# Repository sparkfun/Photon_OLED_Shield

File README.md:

SparkFun Photon OLED Shield
========================================

[*SparkFun Photon OLED Shield (DEV-13628)*](https://www.sparkfun.com/products/13628)

The [SparkFun Photon OLED Shield](https://www.sparkfun.com/products/13231) breaks out a small monochrome, blue-on-black OLED to use with your Photon module. Its micro, but it still packs a punch  the OLED display is crisp, and you can fit a deceivingly large amount of graphics on there. This shield is perfect for adding graphics to your Photon, displaying diagnostic information without resorting to serial output, and teaching a little game theory.

Repository Contents
-------------------

* **/Hardware** - Eagle design files (.brd, .sch)
* **/Production** - Production panel files (.brd)
* **/Libraries** - Firmware library and example code for the Particle Photon.

Documentation
--------------
* **[Hookup Guide](https://learn.sparkfun.com/tutorials/photon-oled-shield-hookup-guide)** - Hardware overview and example code.

Product Versions
----------------
* [DEV-13628](https://www.sparkfun.com/products/13628)- V1.0 release of the Photon OLED Shield.

License Information
-------------------
This product is _**open source**_! 

The **hardware** is released under [Creative Commons ShareAlike 4.0 International](https://creativecommons.org/licenses/by-sa/4.0/).

The **code**  license can be found in the source directory.

Please use, reuse, and modify these files as you see fit. Please maintain attribution to SparkFun Electronics and release anything derivative under the same license.

Distributed as-is; no warranty is given.

- Your friends at SparkFun.

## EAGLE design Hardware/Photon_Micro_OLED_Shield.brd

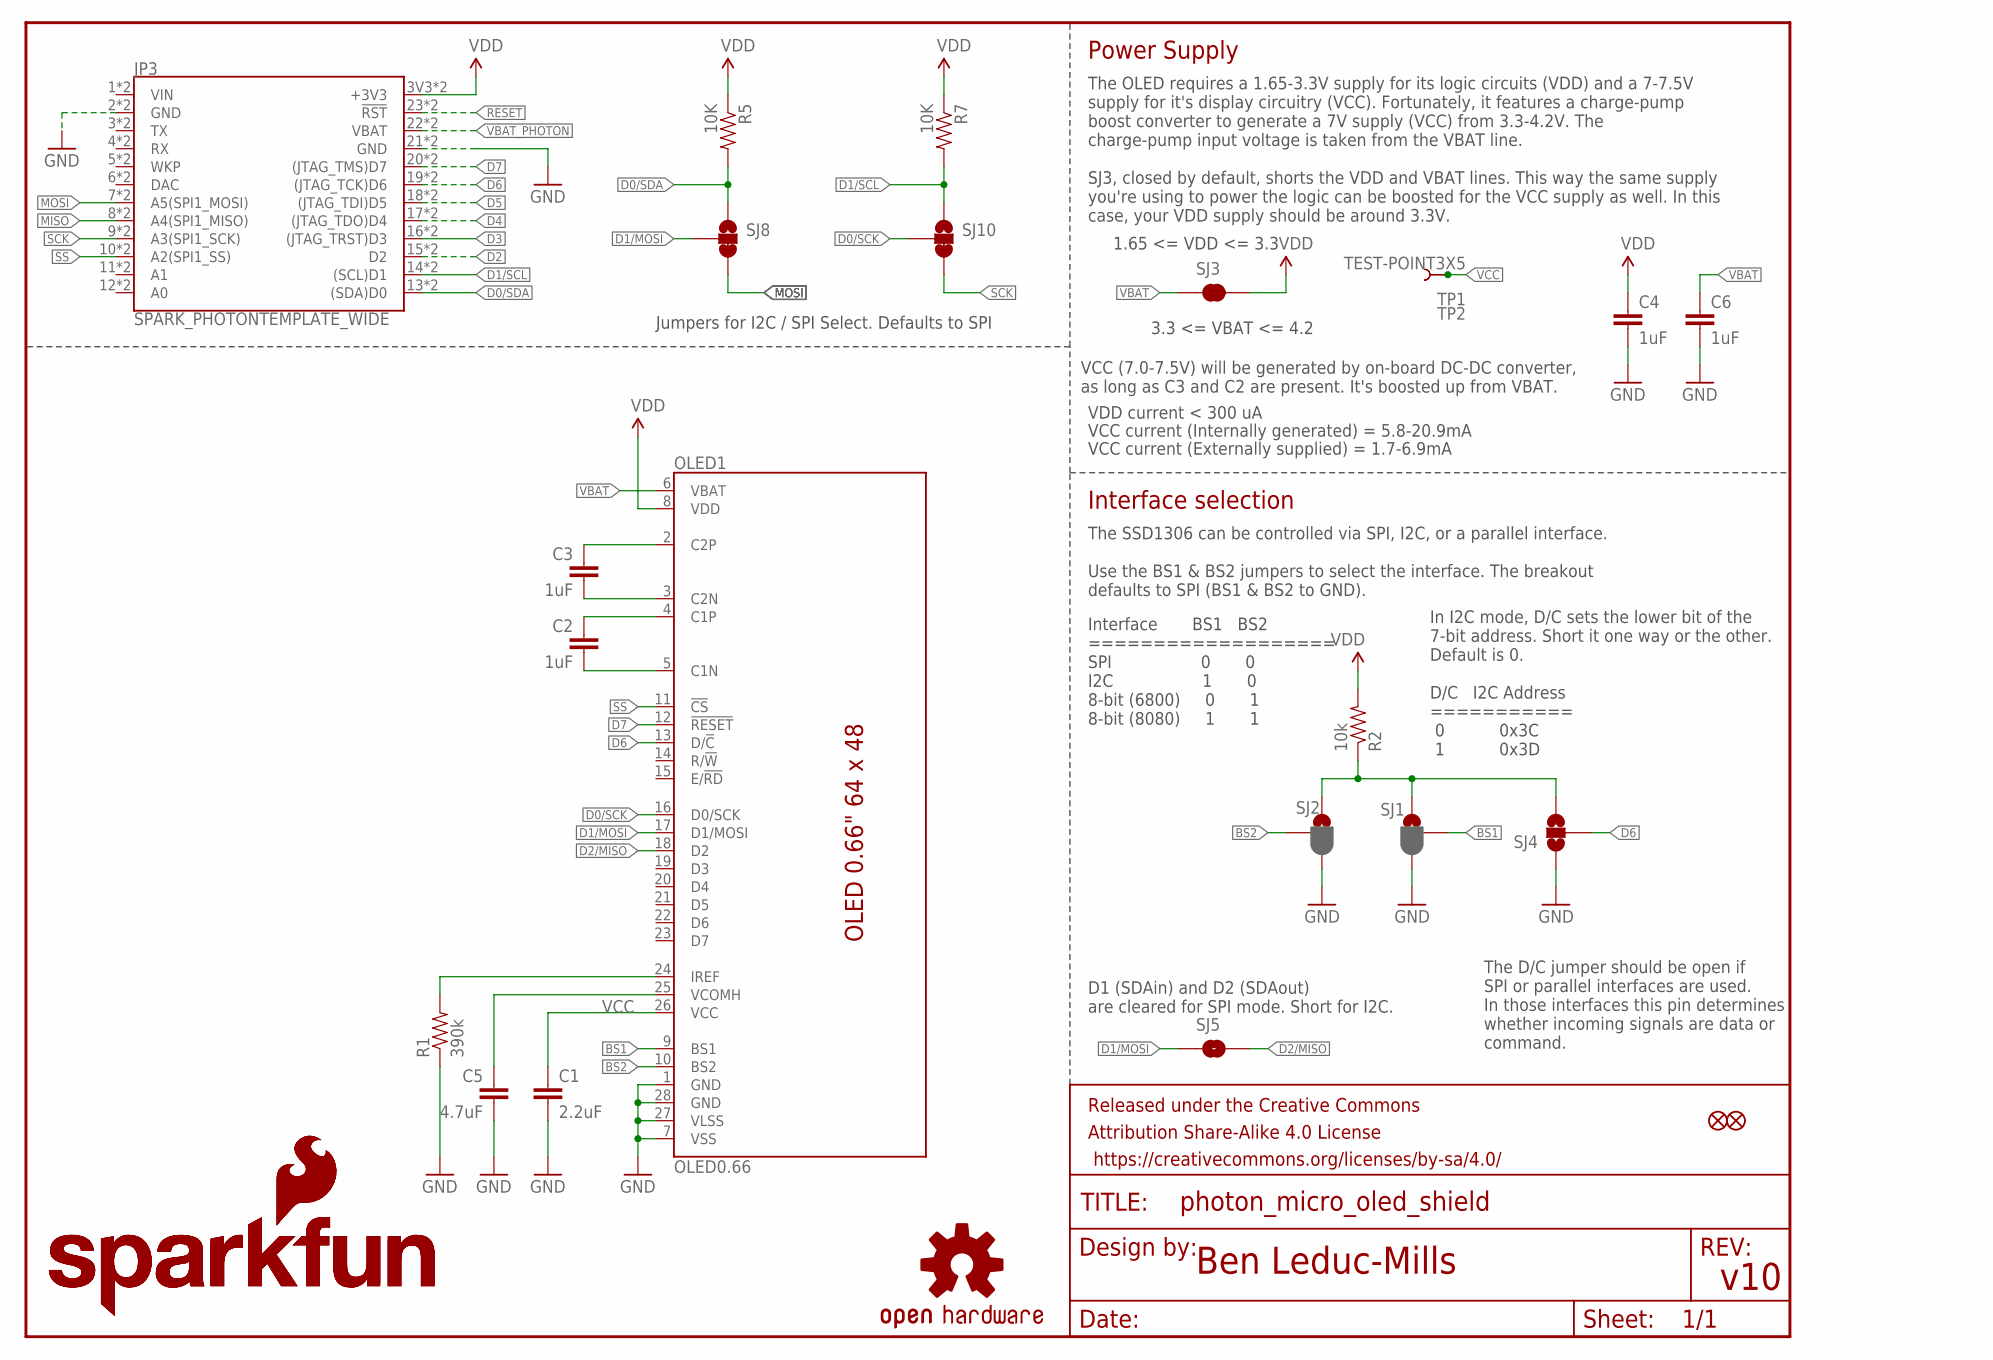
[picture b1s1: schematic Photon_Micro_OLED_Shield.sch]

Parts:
C1: 2.2uF; 0805-CAP
C2, C3: 1uF; 0805-CAP
C4, C6: 1uF; 0603-CAP
C5: 4.7uF; 1206-CAP
FID1, FID2: FIDUCIAL1X2; FIDUCIAL-1X2
FRAME1: FRAME-LETTER; CREATIVE_COMMONS
JP3: SPARK_PHOTONTEMPLATE_WIDE; SPARK_PHOTON_TEMPLATE_WIDE
LOGO1, LOGO2: SFE_LOGO_NAME_FLAME.1_INCH; SFE_LOGO_NAME_FLAME_.1
LOGO3: OSHW-LOGOS; OSHW-LOGO-S
OLED1: OLED0.66; OLED-0.66-64X48
R1: 390k; 0603-RES
R2: 10k; 0603-RES
R5, R7: 10K; 0603-RES
SJ1: BS1; PAD-JUMPER-3-2OF3_NC_BY_PASTE_YES_SILK_FULL_BOX
SJ2: BS2; PAD-JUMPER-3-2OF3_NC_BY_PASTE_YES_SILK_FULL_BOX
SJ3: JUMPER-PAD-2-NC_BY_TRACE; PAD-JUMPER-2-NC_BY_TRACE_YES_SILK
SJ4: JUMPER-PAD-3-NOYES_SILK; PAD-JUMPER-3-NO_YES_SILK
SJ5: JUMPER-PAD-2-NOYES_SILK; PAD-JUMPER-2-NO_YES_SILK
SJ8, SJ10: JUMPER-PAD-3-2OF3_NC_BY_TRACE_SMALL; PAD-JUMPER-3-2OF3_NC_BY_TRACE_YES_SILK_FULL_BOX
TP1, TP2: TEST-POINT3X5; PAD.03X.05

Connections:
BS1: OLED1.9 (BS1), SJ1.2
BS2: OLED1.10 (BS2), SJ2.2
C1N: C2.2, OLED1.5 (C1N)
C1P: C2.1, OLED1.4 (C1P)
C2N: C3.2, OLED1.3 (C2N)
C2P: C3.1, OLED1.2 (C2P)
D0/SCK: OLED1.16 (D0/SCK), SJ10.2
D0/SDA: JP3.13 ((SDA)D0), JP3.D0 ((SDA)D0), R5.2, SJ8.1
D1/MOSI: OLED1.17 (D1/MOSI), SJ5.1, SJ8.2
D1/SCL: JP3.14 ((SCL)D1), JP3.D1 ((SCL)D1), R7.2, SJ10.1
D2: JP3.15 (D2), JP3.D2
D2/MISO: OLED1.18 (D2), SJ5.2
D3: JP3.16 ((JTAG_TRST)D3), JP3.D3 ((JTAG_TRST)D3)
D4: JP3.17 ((JTAG_TDO)D4), JP3.D4 ((JTAG_TDO)D4)
D5: JP3.18 ((JTAG_TDI)D5), JP3.D5 ((JTAG_TDI)D5)
D6: JP3.19 ((JTAG_TCK)D6), JP3.D6 ((JTAG_TCK)D6), OLED1.13 (D/!C!), SJ4.2
D7: JP3.20 ((JTAG_TMS)D7), JP3.D7 ((JTAG_TMS)D7), OLED1.12 (!RESET!)
GND: C1.2, C4.2, C5.2, C6.2, JP3.2 (GND), JP3.21 (GND), JP3.GND@0 (GND), JP3.GND@2 (GND), OLED1.1 (GND), OLED1.7 (VSS), OLED1.27 (VLSS), OLED1.28 (GND), R1.1, SJ1.3, SJ2.3, SJ4.1
IREF: OLED1.24 (IREF), R1.2
MISO: JP3.8 (A4(SPI1_MISO)), JP3.A4 (A4(SPI1_MISO))
MOSI: JP3.7 (A5(SPI1_MOSI)), JP3.A5 (A5(SPI1_MOSI)), SJ8.3
RESET: JP3.23 (!RST!), JP3.RST (!RST!)
SCK: JP3.9 (A3(SPI1_SCK)), JP3.A3 (A3(SPI1_SCK)), SJ10.3
SS: JP3.10 (A2(SPI1_SS)), JP3.A2 (A2(SPI1_SS)), OLED1.11 (!CS!)
VBAT: C6.1, OLED1.6 (VBAT), SJ3.1
VBAT_PHOTON: JP3.22 (VBAT), JP3.VBAT
VCC: C1.1, OLED1.26 (VCC), TP1.P$1, TP2.P$1
VCOMH: C5.1, OLED1.25 (VCOMH)
VDD: C4.1, JP3.3V3 (+3V3), JP3.24 (+3V3), OLED1.8 (VDD), R2.2, R5.1, R7.1, SJ3.2
VDD_PU: R2.1, SJ1.1, SJ2.1, SJ4.3

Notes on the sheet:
v10
Ben Leduc-Mills
1.65 <= VDD <= 3.3
VDD current < 300 uA
VCC current (Internally generated) = 5.8-20.9mA
VCC current (Externally supplied) = 1.7-6.9mA
Interface BS1 BS2 =================== SPI 0 0 I2C 1 0 8-bit (6800) 0 1 8-bit (8080) 1 1
VCC (7.0-7.5V) will be generated by on-board DC-DC converter, as long as C3 and C2 are present. It's boosted up from VBAT.
3.3 <= VBAT <= 4.2
Interface selection
D1 (SDAin) and D2 (SDAout) are cleared for SPI mode. Short for I2C.
The SSD1306 can be controlled via SPI, I2C, or a parallel interface. Use the BS1 & BS2 jumpers to select the interface. The breakout defaults to SPI (BS1 & BS2 to GND).
In I2C mode, D/C sets the lower bit of the 7-bit address. Short it one way or the other. Default is 0. D/C I2C Address =========== 0 0x3C 1 0x3D
Power Supply
The OLED requires a 1.65-3.3V supply for its logic circuits (VDD) and a 7-7.5V supply for it's display circuitry (VCC). Fortunately, it features a charge-pump boost converter to generate a 7V supply (VCC) from 3.3-4.2V. The charge-pump input voltage is taken from the VBAT line. SJ3, closed by defau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
The D/C jumper should be open if SPI or parallel interfaces are used. In those interfaces this pin determines whether incoming signals are data or command.
Jumpers for I2C / SPI Select. Defaults to SPI

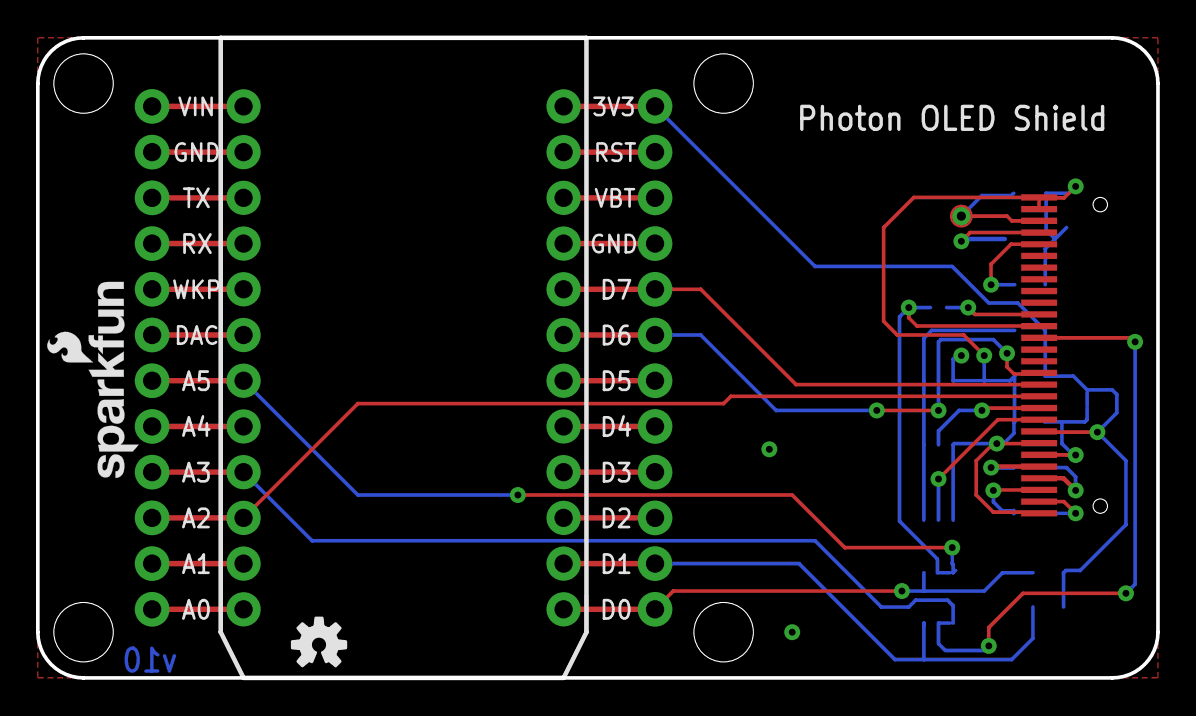
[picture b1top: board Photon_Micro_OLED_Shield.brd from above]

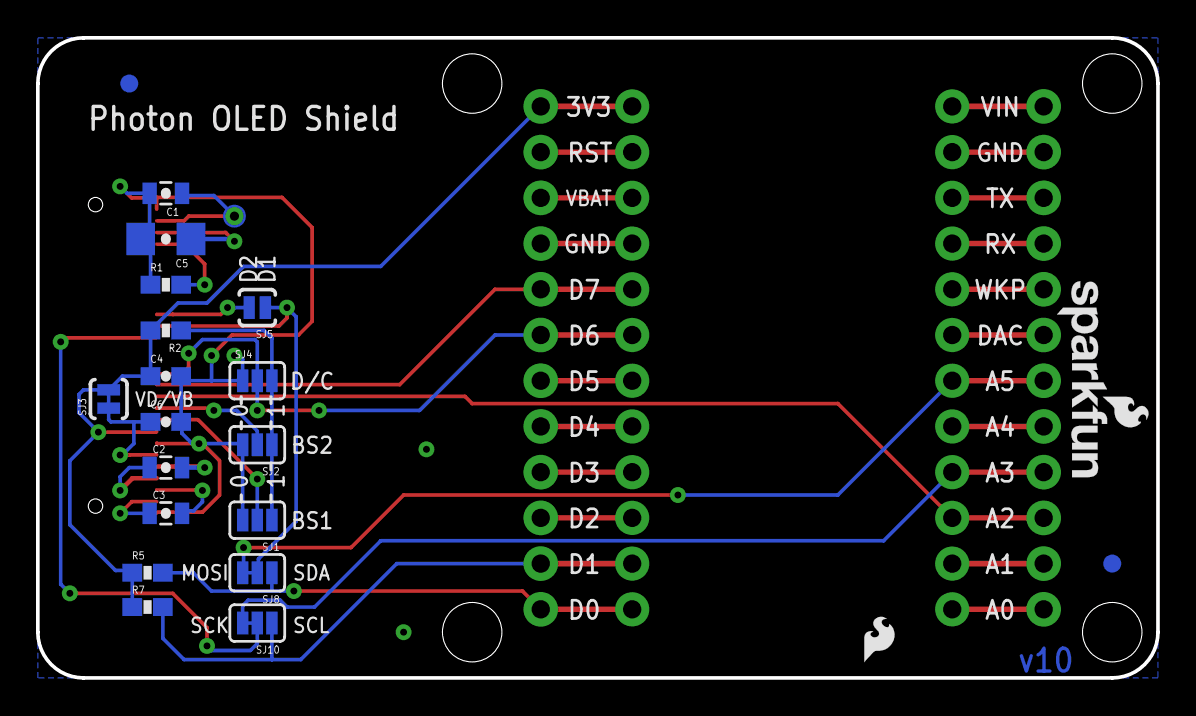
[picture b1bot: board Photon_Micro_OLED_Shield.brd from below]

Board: 2 copper layers, 62.2 x 35.6 mm, 28 parts (22 on the bottom side), 30 nets.

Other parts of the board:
U$1: SFE_LOGO_FLAME_.1

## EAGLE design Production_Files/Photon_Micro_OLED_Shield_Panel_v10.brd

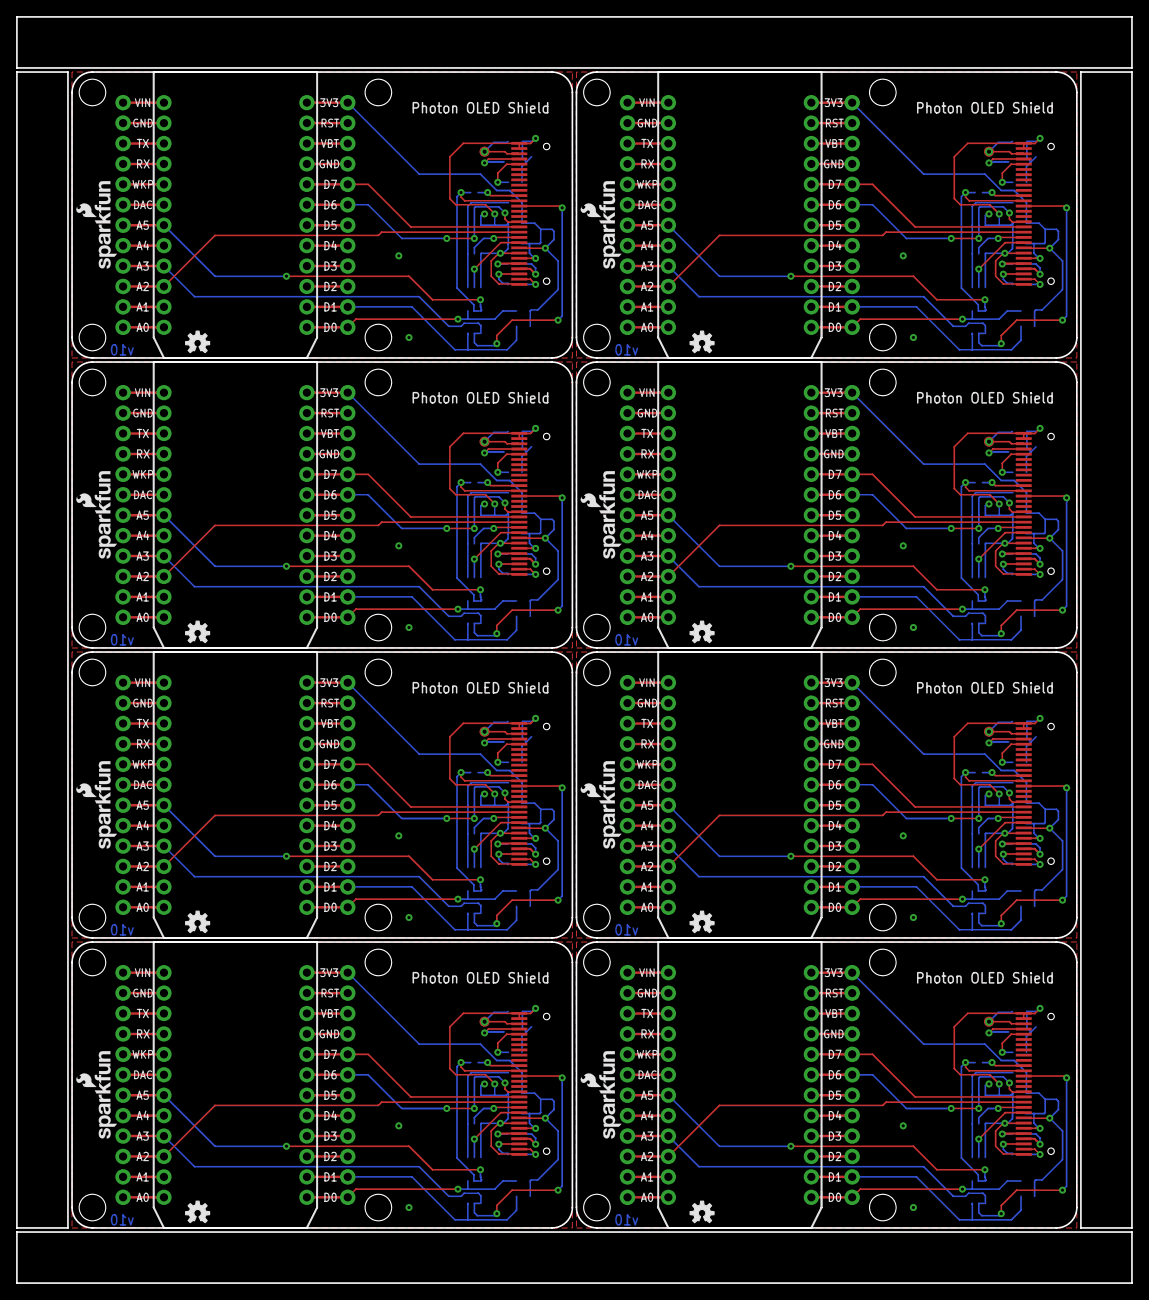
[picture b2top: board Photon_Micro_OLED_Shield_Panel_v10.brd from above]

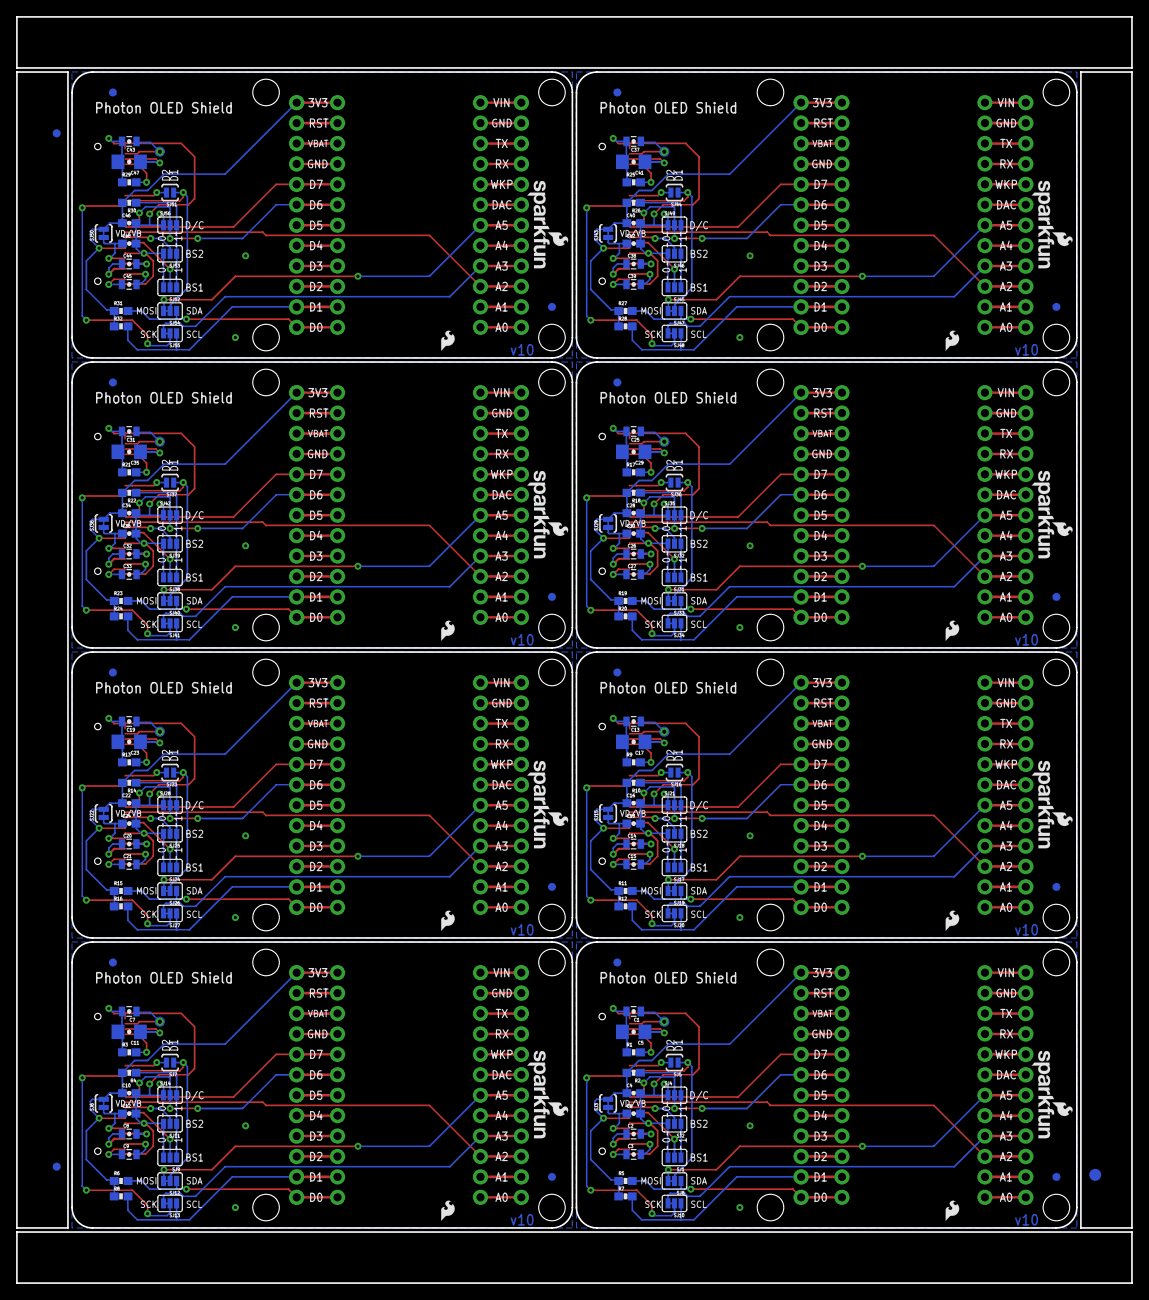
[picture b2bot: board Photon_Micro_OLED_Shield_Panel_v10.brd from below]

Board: 2 copper layers, 138.7 x 157.5 mm, 219 parts (179 on the bottom side), 240 nets.

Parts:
C1, C7, C13, C19, C25, C31, C37, C43: 2.2uF; 0805-CAP
C2, C3, C8, C9, C14, C15, C20, C21, C26, C27, C32, C33, C38, C39, C44, C45: 1uF; 0805-CAP
C4, C6, C10, C12, C16, C18, C22, C24, C28, C30, C34, C36, C40, C42, C46, C48: 1uF; 0603-CAP
C5, C11, C17, C23, C29, C35, C41, C47: 4.7uF; 1206-CAP
E$1: FIDUCIAL-1.5X3
E$4, E$5: FIDUCIAL-1X2
FID1, FID2, FID3, FID4, FID5, FID6, FID7, FID8, FID9, FID10, FID11, FID12, FID13, FID14, FID15, FID16: FIDUCIAL1X2; FIDUCIAL-1X2
JP1, JP2, JP3, JP4, JP5, JP6, JP7, JP8: SPARK_PHOTONTEMPLATE_WIDE; SPARK_PHOTON_TEMPLATE_WIDE
LOGO1, LOGO2, LOGO5, LOGO6, LOGO8, LOGO9, LOGO11, LOGO12, LOGO14, LOGO15, LOGO17, LOGO18, LOGO20, LOGO21, LOGO23, LOGO24: SFE_LOGO_NAME_FLAME.1_INCH; SFE_LOGO_NAME_FLAME_.1
LOGO3, LOGO4, LOGO7, LOGO10, LOGO13, LOGO16, LOGO19, LOGO22: OSHW-LOGOS; OSHW-LOGO-S
OLED1, OLED2, OLED3, OLED4, OLED5, OLED6, OLED7, OLED8: OLED0.66; OLED-0.66-64X48
R1, R3, R9, R13, R17, R21, R25, R29: 390k; 0603-RES
R2, R4, R10, R14, R18, R22, R26, R30: 10k; 0603-RES
R5, R6, R7, R8, R11, R12, R15, R16, R19, R20, R23, R24, R27, R28, R31, R32: 10K; 0603-RES
SJ1, SJ9, SJ17, SJ24, SJ31, SJ38, SJ45, SJ52: BS1; PAD-JUMPER-3-2OF3_NC_BY_PASTE_YES_SILK_FULL_BOX
SJ2, SJ11, SJ18, SJ25, SJ32, SJ39, SJ46, SJ53: BS2; PAD-JUMPER-3-2OF3_NC_BY_PASTE_YES_SILK_FULL_BOX
SJ3, SJ6, SJ15, SJ22, SJ29, SJ36, SJ43, SJ50: PAD-JUMPER-2-NC_BY_TRACE_YES_SILK
SJ4, SJ14, SJ21, SJ28, SJ35, SJ42, SJ49, SJ56: PAD-JUMPER-3-NO_YES_SILK
SJ5, SJ7, SJ16, SJ23, SJ30, SJ37, SJ44, SJ51: PAD-JUMPER-2-NO_YES_SILK
SJ8, SJ10, SJ12, SJ13, SJ19, SJ20, SJ26, SJ27, SJ33, SJ34, SJ40, SJ41, SJ47, SJ48, SJ54, SJ55: PAD-JUMPER-3-2OF3_NC_BY_TRACE_YES_SILK_FULL_BOX
TP1, TP2, TP3, TP4, TP5, TP6, TP7, TP8, TP9, TP10, TP11, TP12, TP13, TP14, TP15, TP16: TEST-POINT3X5; PAD.03X.05
U$1, U$2, U$3, U$4, U$5, U$6, U$7, U$8: SFE_LOGO_FLAME_.1

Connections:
BS1: OLED1.9, SJ1.2
BS2: OLED1.10, SJ2.2
BS3: OLED2.9, SJ9.2
BS4: OLED2.10, SJ11.2
BS5: OLED3.9, SJ17.2
BS6: OLED3.10, SJ18.2
BS7: OLED4.9, SJ24.2
BS8: OLED4.10, SJ25.2
BS9: OLED5.9, SJ31.2
BS10: OLED5.10, SJ32.2
BS11: OLED6.9, SJ38.2
BS12: OLED6.10, SJ39.2
BS13: OLED7.9, SJ45.2
BS14: OLED7.10, SJ46.2
BS15: OLED8.9, SJ52.2
BS16: OLED8.10, SJ53.2
C1N: C2.2, OLED1.5
C1N1: C8.2, OLED2.5
C1N2: C14.2, OLED3.5
C1N3: C20.2, OLED4.5
C1N4: C26.2, OLED5.5
C1N5: C32.2, OLED6.5
C1N6: C38.2, OLED7.5
C1N7: C44.2, OLED8.5
C1P: C2.1, OLED1.4
C1P1: C8.1, OLED2.4
C1P2: C14.1, OLED3.4
C1P3: C20.1, OLED4.4
C1P4: C26.1, OLED5.4
C1P5: C32.1, OLED6.4
C1P6: C38.1, OLED7.4
C1P7: C44.1, OLED8.4
C2N: C3.2, OLED1.3
C2N1: C9.2, OLED2.3
C2N2: C15.2, OLED3.3
C2N3: C21.2, OLED4.3
C2N4: C27.2, OLED5.3
C2N5: C33.2, OLED6.3
C2N6: C39.2, OLED7.3
C2N7: C45.2, OLED8.3
C2P: C3.1, OLED1.2
C2P1: C9.1, OLED2.2
C2P2: C15.1, OLED3.2
C2P3: C21.1, OLED4.2
C2P4: C27.1, OLED5.2
C2P5: C33.1, OLED6.2
C2P6: C39.1, OLED7.2
C2P7: C45.1, OLED8.2
D0/SCK: OLED1.16, SJ10.2
D0/SCK1: OLED2.16, SJ13.2
D0/SCK2: OLED3.16, SJ20.2
D0/SCK3: OLED4.16, SJ27.2
D0/SCK4: OLED5.16, SJ34.2
D0/SCK5: OLED6.16, SJ41.2
D0/SCK6: OLED7.16, SJ48.2
D0/SCK7: OLED8.16, SJ55.2
D0/SDA: JP3.13, JP3.D0, R5.2, SJ8.1
D0/SDA1: JP1.13, JP1.D0, R6.2, SJ12.1
D0/SDA2: JP2.13, JP2.D0, R11.2, SJ19.1
D0/SDA3: JP4.13, JP4.D0, R15.2, SJ26.1
D0/SDA4: JP5.13, JP5.D0, R19.2, SJ33.1
D0/SDA5: JP6.13, JP6.D0, R23.2, SJ40.1
D0/SDA6: JP7.13, JP7.D0, R27.2, SJ47.1
D0/SDA7: JP8.13, JP8.D0, R31.2, SJ54.1
D1: JP1.20, JP1.D7, OLED2.12
D1/MOSI: OLED1.17, SJ5.1, SJ8.2
D1/MOSI1: OLED2.17, SJ7.1, SJ12.2
D1/MOSI2: OLED3.17, SJ16.1, SJ19.2
D1/MOSI3: OLED4.17, SJ23.1, SJ26.2
D1/MOSI4: OLED5.17, SJ30.1, SJ33.2
D1/MOSI5: OLED6.17, SJ37.1, SJ40.2
D1/MOSI6: OLED7.17, SJ44.1, SJ47.2
D1/MOSI7: OLED8.17, SJ51.1, SJ54.2
D1/SCL: JP3.14, JP3.D1, R7.2, SJ10.1
D1/SCL1: JP1.14, JP1.D1, R8.2, SJ13.1
D1/SCL2: JP2.14, JP2.D1, R12.2, SJ20.1
D1/SCL3: JP4.14, JP4.D1, R16.2, SJ27.1
D1/SCL4: JP5.14, JP5.D1, R20.2, SJ34.1
D1/SCL5: JP6.14, JP6.D1, R24.2, SJ41.1
D1/SCL6: JP7.14, JP7.D1, R28.2, SJ48.1
D1/SCL7: JP8.14, JP8.D1, R32.2, SJ55.1
D2: JP3.15, JP3.D2
D2/MISO: OLED1.18, SJ5.2
D2/MISO1: OLED2.18, SJ7.2
D2/MISO2: OLED3.18, SJ16.2
D2/MISO3: OLED4.18, SJ23.2
D2/MISO4: OLED5.18, SJ30.2
D2/MISO5: OLED6.18, SJ37.2
D2/MISO6: OLED7.18, SJ44.2
D2/MISO7: OLED8.18, SJ51.2
D3: JP3.16, JP3.D3
D4: JP3.17, JP3.D4
D5: JP3.18, JP3.D5
D6: JP3.19, JP3.D6, OLED1.13, SJ4.2
D7: JP3.20, JP3.D7, OLED1.12
D8: JP1.19, JP1.D6, OLED2.13, SJ14.2
D9: JP1.18, JP1.D5
D10: JP1.17, JP1.D4
D11: JP1.15, JP1.D2
D12: JP1.16, JP1.D3
D13: JP2.20, JP2.D7, OLED3.12
D14: JP2.19, JP2.D6, OLED3.13, SJ21.2
D15: JP2.18, JP2.D5
D16: JP2.17, JP2.D4
D17: JP2.15, JP2.D2
D18: JP2.16, JP2.D3
D19: JP4.20, JP4.D7, OLED4.12
D20: JP4.19, JP4.D6, OLED4.13, SJ28.2
D21: JP4.18, JP4.D5
D22: JP4.17, JP4.D4
D23: JP4.15, JP4.D2
D24: JP4.16, JP4.D3
D25: JP5.20, JP5.D7, OLED5.12
D26: JP5.19, JP5.D6, OLED5.13, SJ35.2
D27: JP5.18, JP5.D5
D28: JP5.17, JP5.D4
D29: JP5.15, JP5.D2
D30: JP5.16, JP5.D3
D31: JP6.20, JP6.D7, OLED6.12
D32: JP6.19, JP6.D6, OLED6.13, SJ42.2
D33: JP6.18, JP6.D5
D34: JP6.17, JP6.D4
D35: JP6.15, JP6.D2
D36: JP6.16, JP6.D3
D37: JP7.20, JP7.D7, OLED7.12
D38: JP7.19, JP7.D6, OLED7.13, SJ49.2
D39: JP7.18, JP7.D5
D40: JP7.17, JP7.D4
D41: JP7.15, JP7.D2
D42: JP7.16, JP7.D3
D43: JP8.20, JP8.D7, OLED8.12
D44: JP8.19, JP8.D6, OLED8.13, SJ56.2
D45: JP8.18, JP8.D5
D46: JP8.17, JP8.D4
D47: JP8.15, JP8.D2
D48: JP8.16, JP8.D3
GND: C1.2, C4.2, C5.2, C6.2, JP3.2, JP3.21, JP3.GND@0, JP3.GND@2, OLED1.1, OLED1.7, OLED1.27, OLED1.28, R1.1, SJ1.3, SJ2.3, SJ4.1
GND1: C7.2, C10.2, C11.2, C12.2, JP1.2, JP1.21, JP1.GND@0, JP1.GND@2, OLED2.1, OLED2.7, OLED2.27, OLED2.28, R3.1, SJ9.3, SJ11.3, SJ14.1
GND2: C13.2, C16.2, C17.2, C18.2, JP2.2, JP2.21, JP2.GND@0, JP2.GND@2, OLED3.1, OLED3.7, OLED3.27, OLED3.28, R9.1, SJ17.3, SJ18.3, SJ21.1
GND3: C19.2, C22.2, C23.2, C24.2, JP4.2, JP4.21, JP4.GND@0, JP4.GND@2, OLED4.1, OLED4.7, OLED4.27, OLED4.28, R13.1, SJ24.3, SJ25.3, SJ28.1
GND4: C25.2, C28.2, C29.2, C30.2, JP5.2, JP5.21, JP5.GND@0, JP5.GND@2, OLED5.1, OLED5.7, OLED5.27, OLED5.28, R17.1, SJ31.3, SJ32.3, SJ35.1
GND5: C31.2, C34.2, C35.2, C36.2, JP6.2, JP6.21, JP6.GND@0, JP6.GND@2, OLED6.1, OLED6.7, OLED6.27, OLED6.28, R21.1, SJ38.3, SJ39.3, SJ42.1
GND6: C37.2, C40.2, C41.2, C42.2, JP7.2, JP7.21, JP7.GND@0, JP7.GND@2, OLED7.1, OLED7.7, OLED7.27, OLED7.28, R25.1, SJ45.3, SJ46.3, SJ49.1
GND7: C43.2, C46.2, C47.2, C48.2, JP8.2, JP8.21, JP8.GND@0, JP8.GND@2, OLED8.1, OLED8.7, OLED8.27, OLED8.28, R29.1, SJ52.3, SJ53.3, SJ56.1
IREF: OLED1.24, R1.2
IREF1: OLED2.24, R3.2
IREF2: OLED3.24, R9.2
IREF3: OLED4.24, R13.2
IREF4: OLED5.24, R17.2
IREF5: OLED6.24, R21.2
IREF6: OLED7.24, R25.2
IREF7: OLED8.24, R29.2
MISO: JP3.8, JP3.A4
MISO1: JP1.8, JP1.A4
MISO2: JP2.8, JP2.A4
MISO3: JP4.8, JP4.A4
MISO4: JP5.8, JP5.A4
MISO5: JP6.8, JP6.A4
MISO6: JP7.8, JP7.A4
MISO7: JP8.8, JP8.A4
MOSI: JP3.7, JP3.A5, SJ8.3
MOSI1: JP1.7, JP1.A5, SJ12.3
MOSI2: JP2.7, JP2.A5, SJ19.3
MOSI3: JP4.7, JP4.A5, SJ26.3
MOSI4: JP5.7, JP5.A5, SJ33.3
MOSI5: JP6.7, JP6.A5, SJ40.3
MOSI6: JP7.7, JP7.A5, SJ47.3
MOSI7: JP8.7, JP8.A5, SJ54.3
RESET: JP3.23, JP3.RST
RESET1: JP1.23, JP1.RST
RESET2: JP2.23, JP2.RST
RESET3: JP4.23, JP4.RST
RESET4: JP5.23, JP5.RST
RESET5: JP6.23, JP6.RST
RESET6: JP7.23, JP7.RST
RESET7: JP8.23, JP8.RST
SCK: JP3.9, JP3.A3, SJ10.3
SCK1: JP1.9, JP1.A3, SJ13.3
SCK2: JP2.9, JP2.A3, SJ20.3
SCK3: JP4.9, JP4.A3, SJ27.3
SCK4: JP5.9, JP5.A3, SJ34.3
SCK5: JP6.9, JP6.A3, SJ41.3
SCK6: JP7.9, JP7.A3, SJ48.3
SCK7: JP8.9, JP8.A3, SJ55.3
SS: JP3.10, JP3.A2, OLED1.11
SS1: JP1.10, JP1.A2, OLED2.11
SS2: JP2.10, JP2.A2, OLED3.11
SS3: JP4.10, JP4.A2, OLED4.11
SS4: JP5.10, JP5.A2, OLED5.11
SS5: JP6.10, JP6.A2, OLED6.11
SS6: JP7.10, JP7.A2, OLED7.11
SS7: JP8.10, JP8.A2, OLED8.11
VBAT: C6.1, OLED1.6, SJ3.1
VBAT1: C12.1, OLED2.6, SJ6.1
VBAT2: C18.1, OLED3.6, SJ15.1
VBAT3: C24.1, OLED4.6, SJ22.1
VBAT4: C30.1, OLED5.6, SJ29.1
VBAT5: C36.1, OLED6.6, SJ36.1
VBAT6: C42.1, OLED7.6, SJ43.1
VBAT7: C48.1, OLED8.6, SJ50.1
VBAT_PHOTON: JP3.22, JP3.VBAT
VBAT_PHOTON1: JP1.22, JP1.VBAT
VBAT_PHOTON2: JP2.22, JP2.VBAT
VBAT_PHOTON3: JP4.22, JP4.VBAT
VBAT_PHOTON4: JP5.22, JP5.VBAT
VBAT_PHOTON5: JP6.22, JP6.VBAT
VBAT_PHOTON6: JP7.22, JP7.VBAT
VBAT_PHOTON7: JP8.22, JP8.VBAT
VCC: C1.1, OLED1.26, TP1.P$1, TP2.P$1
VCC1: C7.1, OLED2.26, TP3.P$1, TP4.P$1
VCC2: C13.1, OLED3.26, TP5.P$1, TP6.P$1
VCC3: C19.1, OLED4.26, TP7.P$1, TP8.P$1
VCC4: C25.1, OLED5.26, TP9.P$1, TP10.P$1
VCC5: C31.1, OLED6.26, TP11.P$1, TP12.P$1
VCC6: C37.1, OLED7.26, TP13.P$1, TP14.P$1
VCC7: C43.1, OLED8.26, TP15.P$1, TP16.P$1
VCOMH: C5.1, OLED1.25
VCOMH1: C11.1, OLED2.25
VCOMH2: C17.1, OLED3.25
VCOMH3: C23.1, OLED4.25
VCOMH4: C29.1, OLED5.25
VCOMH5: C35.1, OLED6.25
VCOMH6: C41.1, OLED7.25
VCOMH7: C47.1, OLED8.25
VDD: C4.1, JP3.3V3, JP3.24, OLED1.8, R2.2, R5.1, R7.1, SJ3.2
VDD1: C10.1, JP1.3V3, JP1.24, OLED2.8, R4.2, R6.1, R8.1, SJ6.2
VDD2: C16.1, JP2.3V3, JP2.24, OLED3.8, R10.2, R11.1, R12.1, SJ15.2
VDD3: C22.1, JP4.3V3, JP4.24, OLED4.8, R14.2, R15.1, R16.1, SJ22.2
VDD4: C28.1, JP5.3V3, JP5.24, OLED5.8, R18.2, R19.1, R20.1, SJ29.2
VDD5: C34.1, JP6.3V3, JP6.24, OLED6.8, R22.2, R23.1, R24.1, SJ36.2
VDD6: C40.1, JP7.3V3, JP7.24, OLED7.8, R26.2, R27.1, R28.1, SJ43.2
VDD7: C46.1, JP8.3V3, JP8.24, OLED8.8, R30.2, R31.1, R32.1, SJ50.2
VDD_PU: R2.1, SJ1.1, SJ2.1, SJ4.3
VDD_PU1: R4.1, SJ9.1, SJ11.1, SJ14.3
VDD_PU2: R10.1, SJ17.1, SJ18.1, SJ21.3
VDD_PU3: R14.1, SJ24.1, SJ25.1, SJ28.3
VDD_PU4: R18.1, SJ31.1, SJ32.1, SJ35.3
VDD_PU5: R22.1, SJ38.1, SJ39.1, SJ42.3
VDD_PU6: R26.1, SJ45.1, SJ46.1, SJ49.3
VDD_PU7: R30.1, SJ52.1, SJ53.1, SJ56.3

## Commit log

2015-03-19 Hardware
    First commit
2015-03-25 qc fixes
2015-04-01 new design
    moved screen to top and extended board so it will work better with the
    rest of the photon shields
2015-05-11 Adding gap between Photon and pin-break outs. Moving D/C to pin D6.
2015-05-11 Reorganizing file structure to match standard.
2015-05-11 Changes per design review (right place)
    Board width fixed to allow space for headers and OLED screen.
2015-05-11 changed board name per new naming conventions
2015-05-22 Revising board name. Zero-ing origin, fixing measures.
2015-05-22 Updating silk. Bringing board edge in a bit.
2015-05-26 Moved fiducially to bottom per issue #8
2015-05-26 issue fix
2015-05-29 created panel v10
2015-07-02 Adding README
2015-07-02 Squashed 'Libraries/Particle/' content from commit 2c31f7a
    git-subtree-dir: Libraries/Particle
    git-subtree-split: 2c31f7a2f374e2f063d3baae99053c5575bd8ada
2015-07-02 Adding Micro OLED Particle library.
2015-08-28 Squashed 'Libraries/Particle/' changes from 2c31f7a..64645c8
    git-subtree-dir: Libraries/Particle
    git-subtree-split: 64645c8c895112b80076cefc5cdf4ac08ec149c7
2015-08-28 Updating subtree commands
2015-09-03 Cleaned up the schematic a lot

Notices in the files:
parts and their libraries:
SparkFun-Aesthetics: Licensing: Creative Commons ShareAlike 4.0 International - https://creativecommons.org/licenses/by-sa/4.0
SparkFun-Aesthetics: Released under the Creative Commons Attribution Share-Alike 4.0 License
SparkFun-Aesthetics: Released under the Creative Commons
